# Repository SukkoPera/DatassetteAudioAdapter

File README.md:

# DatassetteAudioAdapter
DatassetteAudioAdapter is a simple adapter that allows connecting any audio source to the Datassette port of a Commodore VIC-20, 64, 128 or Plus/4 computer.

## Summary
With this adapter, any audio source can be used in place of the proprietary Commodore Datassette, in order to load software into a Commodore computer through the dedicated port.

This project is similar to [MP32C64](https://github.com/SukkoPera/MP32C64) but it is implemented in a slightly different way, with a real opamp for the initial signal amplification. 

It seems to have been originally developed by ZX_Jim, probably inspired by a similar adapter for the ZX Spectrum, which he might have actually developed himself.

In my experience this adapter works just as well as the other one: beside Audio CDs, MP3 files will also work, so a smartphone (provided that you have an old model with an audio jack...) or any other audio player can be used.

PRG files can be converted to audio using the [WAV-PRG](https://wav-prg.sourceforge.io) software suite.

## Assembly
The adapter can either be built with a PJRAN1X1U01X RCA/Cinch connector or with a SJ1-3525N 3.5" headphone jack connector, according to your preference. Note that the RCA connector will point towards the back, while the headphone jack will point to the right.

## Usage
Usage should be straightforward. The only thing to be careful with is the playback volume: start with 0 and gradually increase it until the Signal LED is constantly on. You can still go up a few ticks from there, experiment a bit until you have successful loads.

If the audio player you are using has a volume knob, set the onboard volume control to the maximum and do the above with the knob on the player.

## Releases
If you want to get this board produced, you are recommended to get [the latest release](https://github.com/SukkoPera/DatassetteAudioAdapter/releases) rather than the current git version, as the latter might be under development and is not guaranteed to be working.

Every release is accompanied by its Bill Of Materials (BOM) file and any relevant notes about it, which you are recommended to read carefully.

## License
The DatassetteAudioAdapter documentation, including the design itself, is copyright &copy; SukkoPera 2025 and is licensed under the [Creative Commons Attribution-NonCommercial-ShareAlike 4.0 International License](https://creativecommons.org/licenses/by-nc-sa/4.0/).

This documentation is distributed *as is* and WITHOUT ANY EXPRESS OR IMPLIED WARRANTIES whatsoever with respect to its functionality, operability or use, including, without limitation, any implied warranties OF MERCHANTABILITY, SATISFACTORY QUALITY, FITNESS FOR A PARTICULAR PURPOSE or infringement. We expressly disclaim any liability whatsoever for any direct, indirect, consequential, incidental or special damages, including, without limitation, lost revenues, lost profits, losses resulting from business interruption or loss of data, regardless of the form of action or legal theory under which the liability may be asserted, even if advised of the possibility or likelihood of such damages.

## Support the Project
If you want to get some boards manufactured, you can get them from PCBWay through this link:

You get my gratitude and cheap, professionally-made and good quality PCBs, I get some credit that will help with this and [other projects](https://www.pcbway.com/project/member/shareproject/?bmbid=41100). You won't even have to worry about the various PCB options, it's all pre-configured for you!

Also, if you still have to register, [you can use this link](https://www.pcbway.com/setinvite.aspx?inviteid=41100) to get some bonus initial credit (and yield me some more).

You can also buy me a coffee if you want:

## Thanks
* ZX_Jim for designing the original adapter.

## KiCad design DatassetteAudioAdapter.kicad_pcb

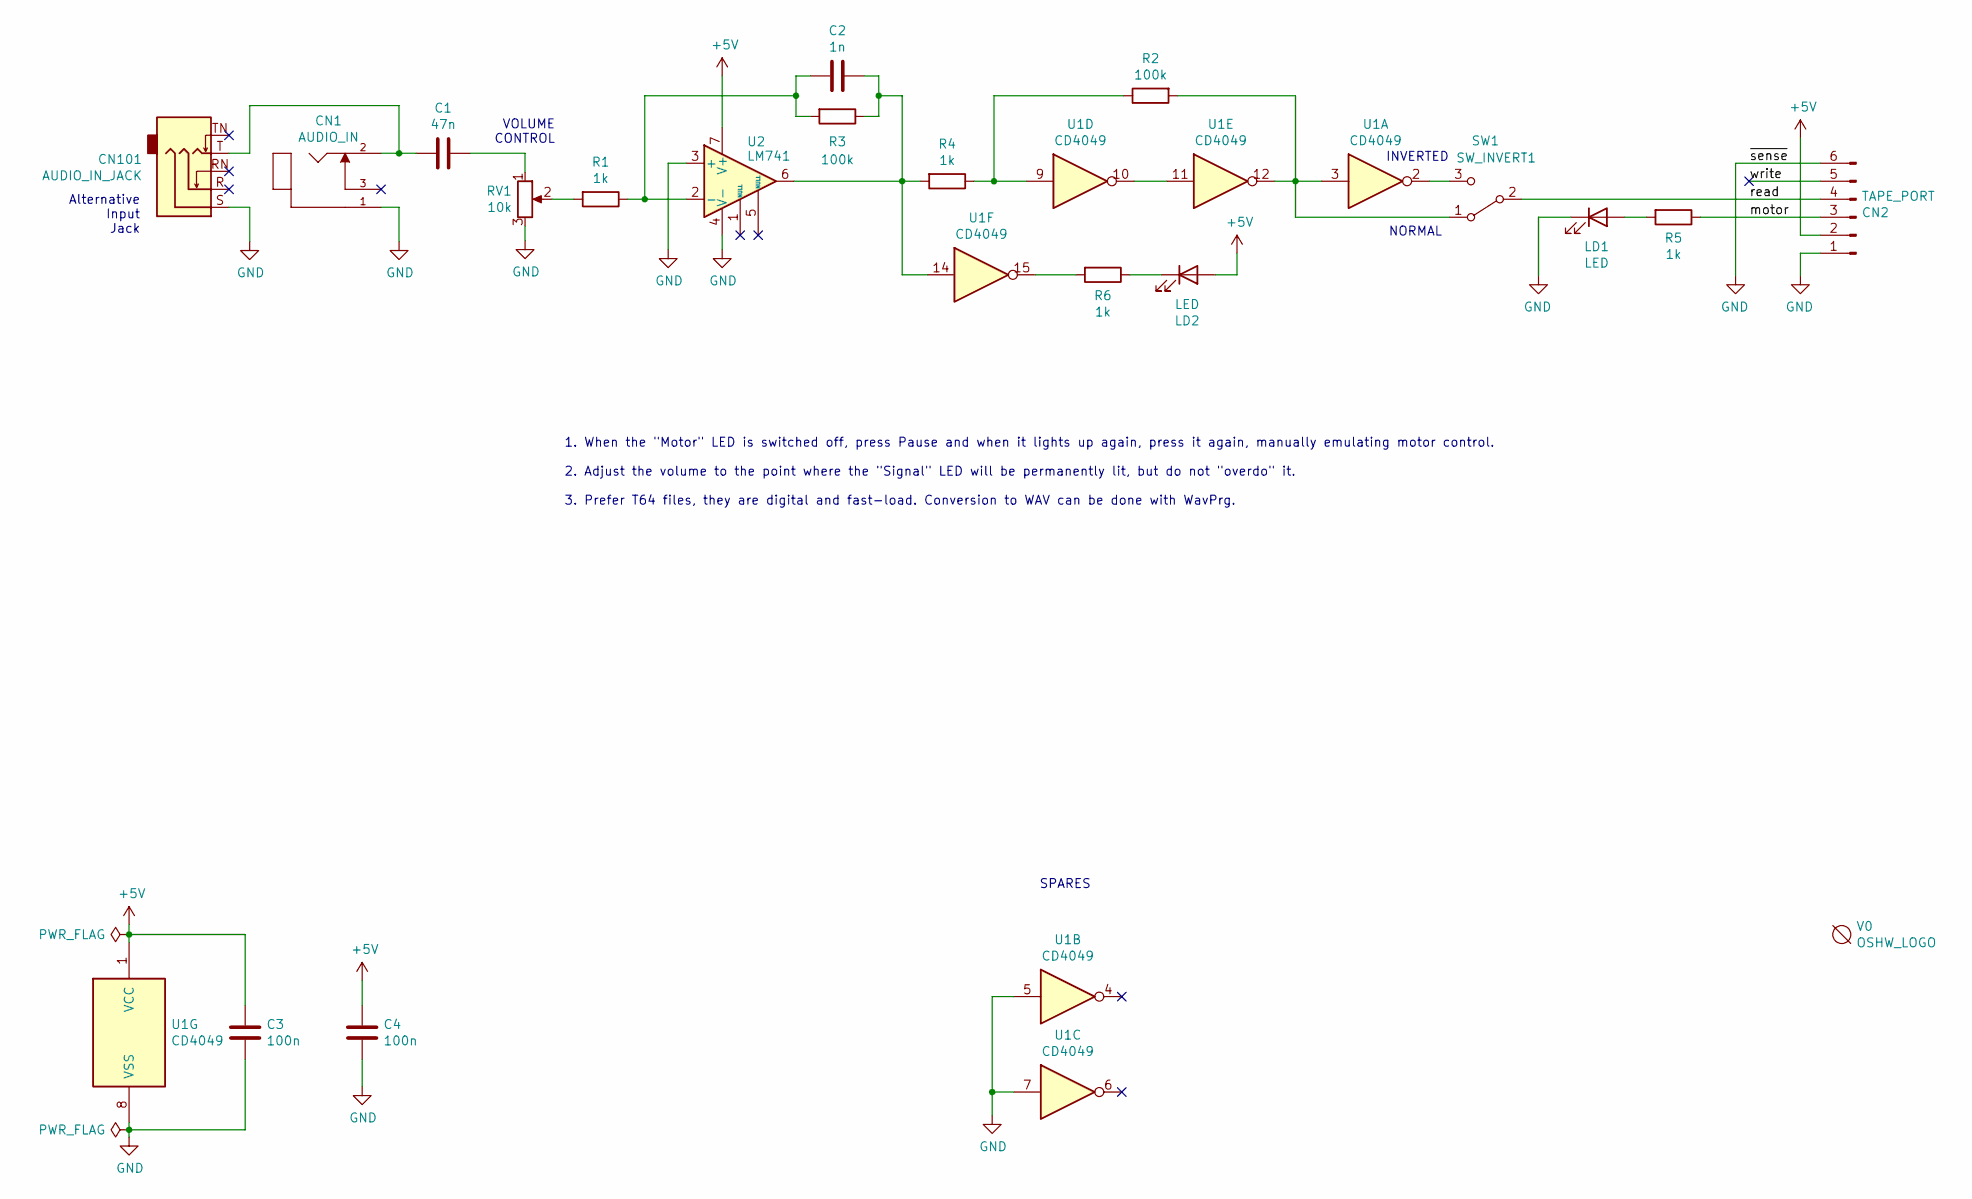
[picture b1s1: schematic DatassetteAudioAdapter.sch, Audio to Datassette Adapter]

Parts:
C1: 47n; C_Disc_D7.0mm_W2.5mm_P5.00mm
C2: 1n; C_Disc_D7.0mm_W2.5mm_P5.00mm
C3, C4: 100n; C_Disc_D7.0mm_W2.5mm_P5.00mm
CN1: AUDIO_IN; SWITCHCRAFT_PJRAN1X1U01X
CN2: TAPE_PORT; C64-Cassette-Port-Female
CN101: AUDIO_IN_JACK; AudioJack_SJ1-3525N
LD1, LD2: LED; LED_D3.0mm
R1, R4, R5, R6: 1k; R_Axial_DIN0207_L6.3mm_D2.5mm_P10.16mm_Horizontal
R2, R3: 100k; R_Axial_DIN0207_L6.3mm_D2.5mm_P10.16mm_Horizontal
RV1: 10k; Pot_Bourns_3306P
SW1: SW_INVERT1; PinHeader_1x03_P2.54mm_Vertical
U1: CD4049; DIP-16_W7.62mm_Socket_LongPads
U2: LM741; DIP-8_W7.62mm_Socket_LongPads
V0: OSHW_LOGO; cc_by_nc_sa_small; MouserPN ---

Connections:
+5V: C3.2, C4.2, CN2.2, LD2.2 (A), U1.1 (VCC), U2.7 (V+)
/motor: CN2.3, R5.1
/read: CN2.4, SW1.2 (B)
/write: CN2.5
GND: C3.1, C4.1, CN1.1, CN2.1, CN2.6, CN101.S, LD1.1 (K), RV1.3, U1.5, U1.7, U1.8 (VSS), U2.3 (+), U2.4 (V-)
unnamed: C1.1, RV1.1
unnamed: C1.2, CN1.2, CN101.T
unnamed: C2.1, R3.1, R4.2, U1.14, U2.6
unnamed: C2.2, R1.1, R3.2, U2.2 (-)
unnamed: LD1.2 (A), R5.2
unnamed: LD2.1 (K), R6.1
unnamed: R1.2, RV1.2
unnamed: R2.1, R4.1, U1.9
unnamed: R2.2, SW1.1 (A), U1.3, U1.12
unnamed: R6.2, U1.15
unnamed: SW1.3 (C), U1.2
unnamed: U1.10, U1.11

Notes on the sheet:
SPARES
VOLUME CONTROL
1. When the "Motor" LED is switched off, press Pause and when it lights up again, press it again, manually emulating motor control. 2. Adjust the volume to the point where the "Signal" LED will be permanently lit, but do not "overdo" it. 3. Prefer T64 files, they are digital and fast-load. Conversi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
Alternative Input Jack
NORMAL
INVERTED

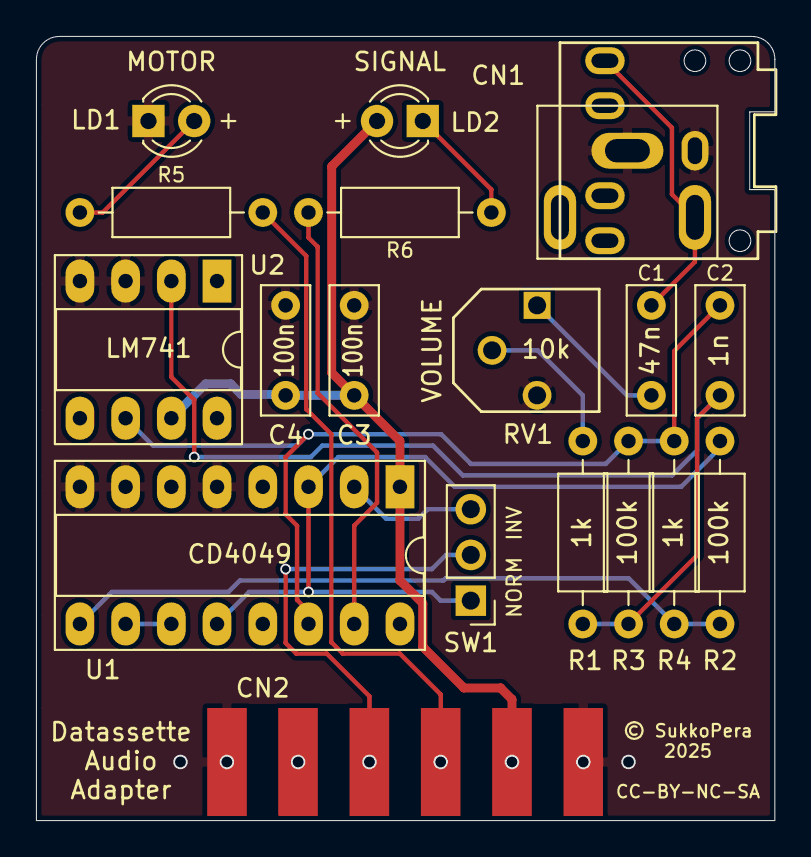
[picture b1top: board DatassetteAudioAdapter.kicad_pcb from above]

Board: 2 copper layers, 41.0 x 43.6 mm, 20 parts (1 on the bottom side), 16 nets.

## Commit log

2025-02-22 Add PCB
2025-03-16 Add 3.5" jack and ready for V1
2025-03-29 Fix volume pot, volume should now increase clockwise
2025-03-29 Add possibility to invert signal
2025-05-21 Fix LEDs
2025-05-21 Fix edge connector orientation, sigh...
2025-05-21 More common component values
2025-06-28 LED resistors -> 1k
2025-06-30 Add README and renders
2025-06-30 CassetteAdapter -> DatassetteAudioAdapter
2026-02-13 Change coffee donation link and image
    Updated the coffee donation link and image in README.

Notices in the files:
DatassetteAudioAdapter.kicad_pcb:
Licensed under CC BY-NC-SA 4.0
